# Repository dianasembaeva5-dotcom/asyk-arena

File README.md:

# Asyk Arena

## What it is & how to play
Asyk Arena is an electronic version of the Kazakh game of asyks. You put asyks on 5 nests, flick the saqa and try to knock them down. Each asyk has a magnet inside, and there is a Hall sensor under each nest, so the arena sees by itself which asyks were knocked down, lights up the nests and counts the points.

## Why I made it
I wanted to take a real Kazakh folk game and show it in a new way, through electronics. Many people know asyks, but few have seen the game count the points by itself.

## How AI helped
I don't know electronics well, so the schematics, PCB layouts and factory files in KiCad were made by AI (Claude). I decided what the arena should do and how complex the circuit should be, checked the result and learned from its files. The idea, the game rules and the arena plan are ours.

*(I wrote this README text in Russian myself and translated it to English with AI.)*

## Full 3D assembly

STEP file: [hardware/3d/asyk_arena_assembly.step](hardware/3d/asyk_arena_assembly.step)

| Part | Details |
|---|---|
| Top plate | birch plywood 400×160×6 mm, 5 holes Ø28 mm every 70 mm for the nest boards |
| Bottom plate | birch plywood 400×160×6 mm, a slot under each nest for the cable |
| Main board | hangs under the bottom plate on 4× M3 brass standoffs 16 mm, Pico facing up |
| Legs | 4× M3 standoffs 30 mm in the corners, also clamp the plates together |

## PCB
**Nest board** (×5)

**Main board**

## Schematic

## Files
| What | Where |
|---|---|
| Nest board (KiCad) | [hardware/nest](hardware/nest) |
| Main board (KiCad) | [hardware/main-board](hardware/main-board) |
| Gerbers, BOM, pick-and-place | `hardware/*/fab/` |
| Arena 3D model (STEP) | [hardware/3d](hardware/3d) |
| Firmware | [firmware](firmware) |

## Demo video (build submission)

## Photos of the final product (build submission)

## BOM
See [bom.csv](bom.csv).

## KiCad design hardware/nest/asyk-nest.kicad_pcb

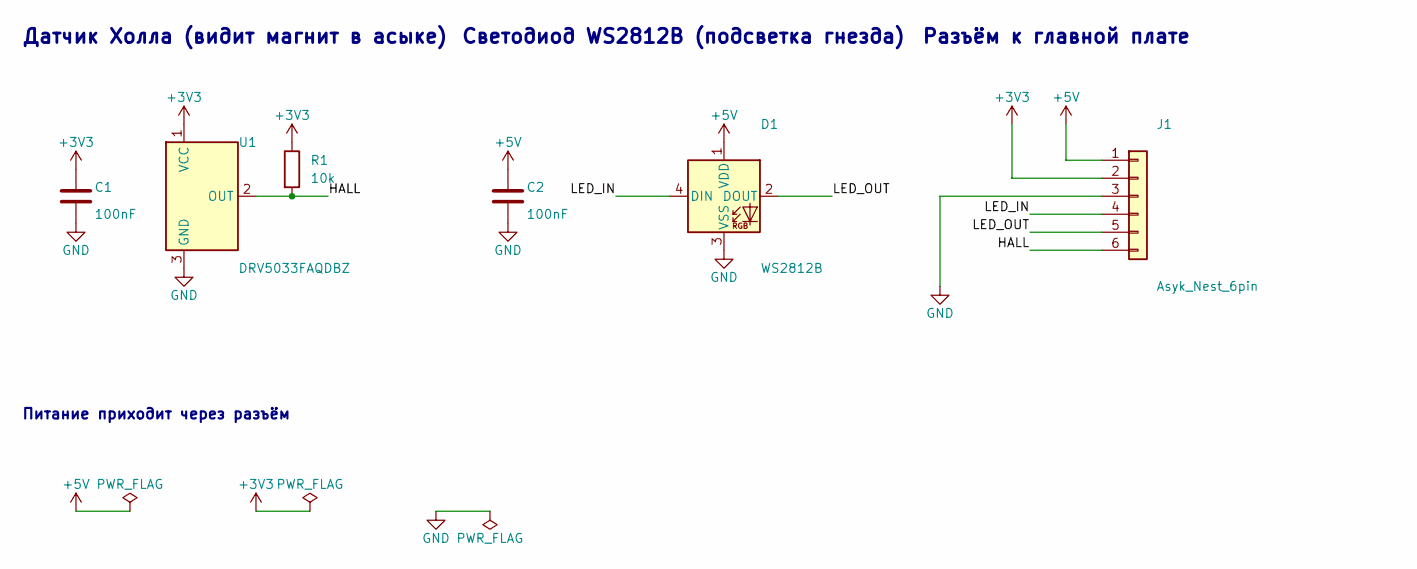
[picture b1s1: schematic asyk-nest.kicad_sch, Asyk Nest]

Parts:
C1, C2: 100nF; C_0603_1608Metric
D1: WS2812B; LED_WS2812B_PLCC4_5.0x5.0mm_P3.2mm
J1: Asyk_Nest_6pin; JST_PH_B6B-PH-K_1x06_P2.00mm_Vertical
R1: 10k; R_0603_1608Metric
U1: DRV5033FAQDBZ; SOT-23

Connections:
+3V3: C1.1, J1.2, R1.1, U1.1 (VCC)
+5V: C2.1, D1.1 (VDD), J1.1
/HALL: J1.6, R1.2, U1.2 (OUT)
/LED_IN: D1.4 (DIN), J1.4
/LED_OUT: D1.2 (DOUT), J1.5
GND: C1.2, C2.2, D1.3 (VSS), J1.3, U1.3 (GND)

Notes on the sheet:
Датчик Холла (видит магнит в асыке)
Светодиод WS2812B (подсветка гнезда)
Разъём к главной плате
Питание приходит через разъём

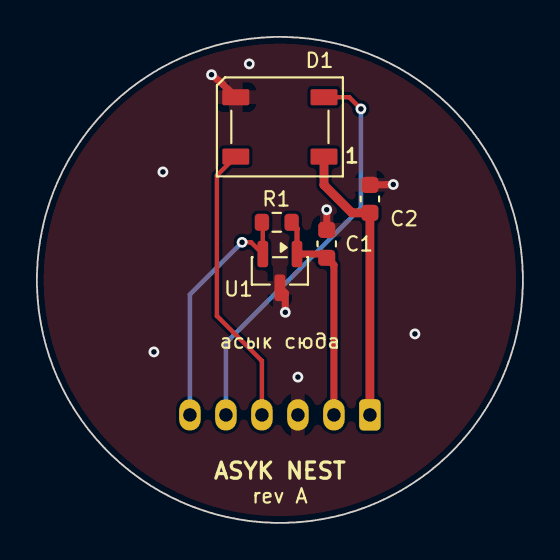
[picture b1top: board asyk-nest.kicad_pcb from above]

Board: 2 copper layers, 27.0 x 27.0 mm, 6 parts (1 on the bottom side), 6 nets.

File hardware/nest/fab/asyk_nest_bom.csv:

"Reference","Value","Footprint","QUANTITY"
"C1,C2","100nF","Capacitor_SMD:C_0603_1608Metric","2"
"D1","WS2812B","LED_SMD:LED_WS2812B_PLCC4_5.0x5.0mm_P3.2mm","1"
"J1","Asyk_Nest_6pin","Connector_JST:JST_PH_B6B-PH-K_1x06_P2.00mm_Vertical","1"
"R1","10k","Resistor_SMD:R_0603_1608Metric","1"
"U1","DRV5033FAQDBZ","Package_TO_SOT_SMD:SOT-23","1"

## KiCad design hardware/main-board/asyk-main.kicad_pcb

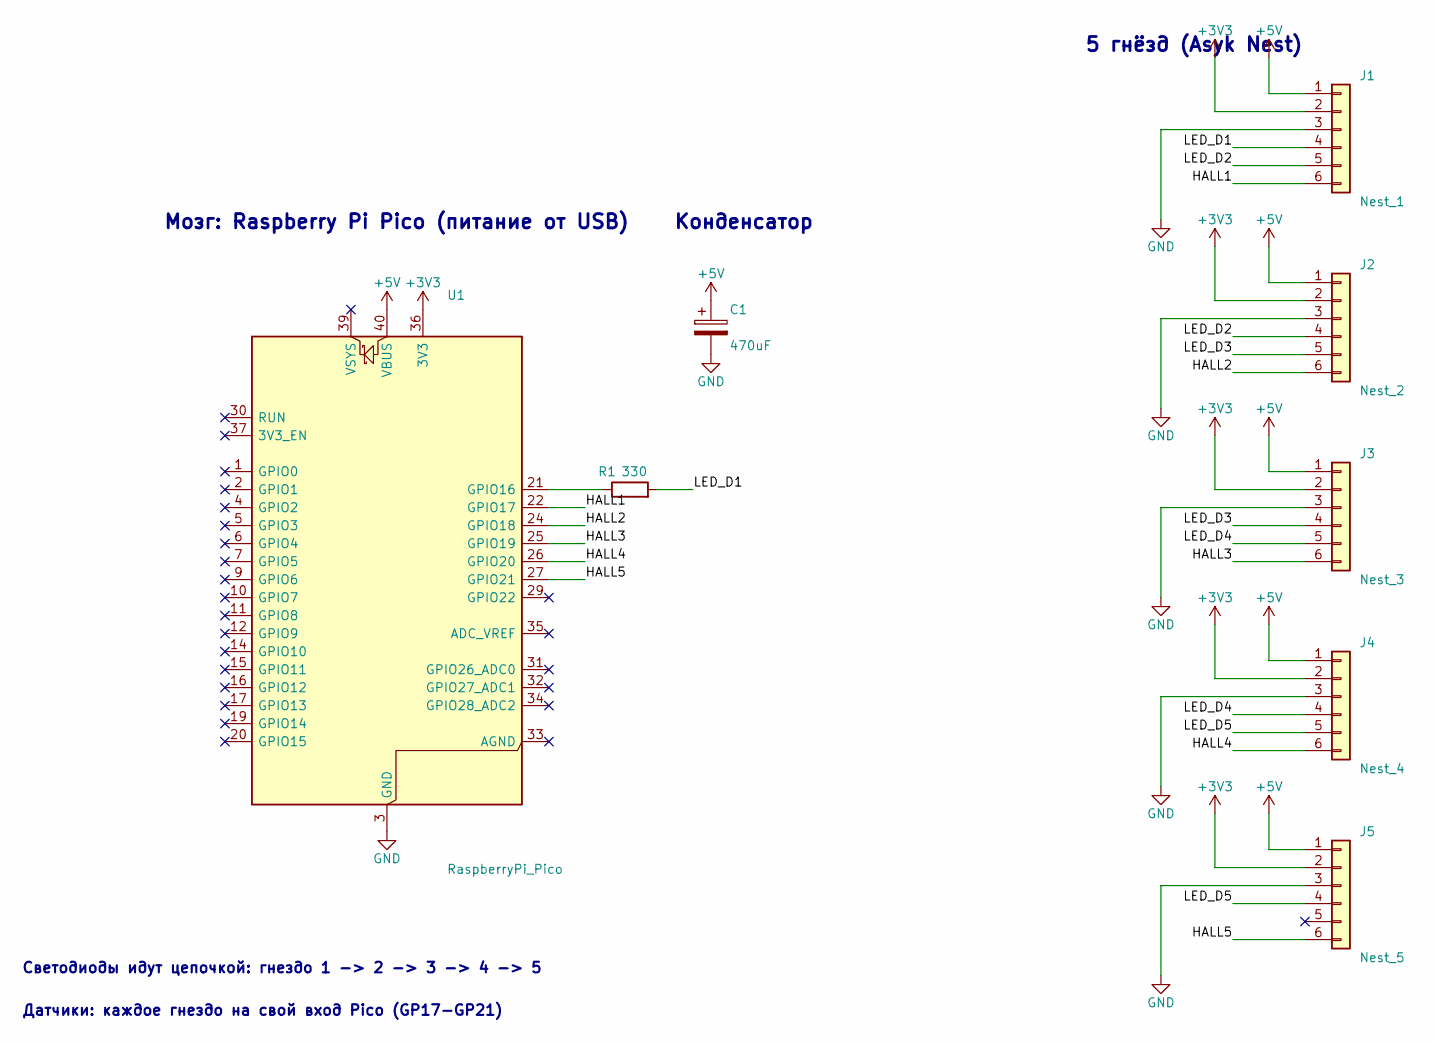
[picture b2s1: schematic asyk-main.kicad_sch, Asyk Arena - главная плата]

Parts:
C1: 470uF; CP_Radial_D8.0mm_P3.50mm
J1: Nest_1; JST_PH_B6B-PH-K_1x06_P2.00mm_Vertical
J2: Nest_2; JST_PH_B6B-PH-K_1x06_P2.00mm_Vertical
J3: Nest_3; JST_PH_B6B-PH-K_1x06_P2.00mm_Vertical
J4: Nest_4; JST_PH_B6B-PH-K_1x06_P2.00mm_Vertical
J5: Nest_5; JST_PH_B6B-PH-K_1x06_P2.00mm_Vertical
R1: 330; R_0603_1608Metric
U1: RaspberryPi_Pico; RaspberryPi_Pico_Common_THT

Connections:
+3V3: J1.2, J2.2, J3.2, J4.2, J5.2, U1.36 (3V3)
+5V: C1.1, J1.1, J2.1, J3.1, J4.1, J5.1, U1.40 (VBUS)
/HALL1: J1.6, U1.22 (GPIO17)
/HALL2: J2.6, U1.24 (GPIO18)
/HALL3: J3.6, U1.25 (GPIO19)
/HALL4: J4.6, U1.26 (GPIO20)
/HALL5: J5.6, U1.27 (GPIO21)
/LED_D1: J1.4, R1.2
/LED_D2: J1.5, J2.4
/LED_D3: J2.5, J3.4
/LED_D4: J3.5, J4.4
/LED_D5: J4.5, J5.4
GND: C1.2, J1.3, J2.3, J3.3, J4.3, J5.3, U1.3 (GND), U1.8 (GND), U1.13 (GND), U1.18 (GND), U1.23 (GND), U1.28 (GND), U1.38 (GND)
unnamed: R1.1, U1.21 (GPIO16)

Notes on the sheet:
Мозг: Raspberry Pi Pico (питание от USB)
Конденсатор
5 гнёзд (Asyk Nest)
Светодиоды идут цепочкой: гнездо 1 -> 2 -> 3 -> 4 -> 5
Датчики: каждое гнездо на свой вход Pico (GP17-GP21)

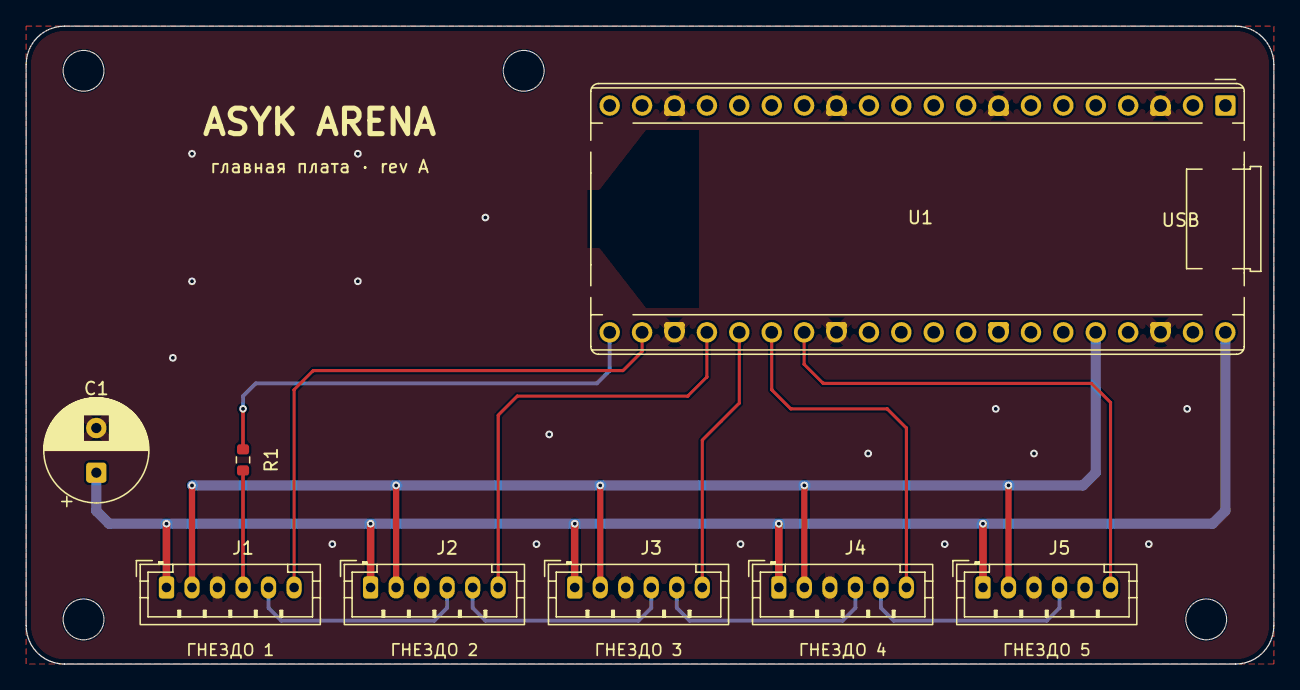
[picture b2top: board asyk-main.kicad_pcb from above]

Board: 2 copper layers, 97.8 x 50.0 mm, 12 parts (0 on the bottom side), 14 nets.

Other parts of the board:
H1, H2, H3, H4: MountingHole_3.2mm_M3

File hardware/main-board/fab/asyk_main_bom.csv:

"Reference","Value","Footprint","QUANTITY"
"C1","470uF","Capacitor_THT:CP_Radial_D8.0mm_P3.50mm","1"
"J1","Nest_1","Connector_JST:JST_PH_B6B-PH-K_1x06_P2.00mm_Vertical","1"
"J2","Nest_2","Connector_JST:JST_PH_B6B-PH-K_1x06_P2.00mm_Vertical","1"
"J3","Nest_3","Connector_JST:JST_PH_B6B-PH-K_1x06_P2.00mm_Vertical","1"
"J4","Nest_4","Connector_JST:JST_PH_B6B-PH-K_1x06_P2.00mm_Vertical","1"
"J5","Nest_5","Connector_JST:JST_PH_B6B-PH-K_1x06_P2.00mm_Vertical","1"
"R1","330","Resistor_SMD:R_0603_1608Metric","1"
"U1","RaspberryPi_Pico","Module:RaspberryPi_Pico_Common_THT","1"
